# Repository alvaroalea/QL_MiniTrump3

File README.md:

# SINCLAIR QL Mini Trump Card 3 Disk Interface

(C) 2024 Alvaro Alea Fernandez

License under: CERN Open Hardware Licence Version 2 - Strongly Reciprocal

https://ohwr.org/cern_ohl_s_v2.txt

This is a new PCB for the well know Trump Card Interface.

WARNING: This board include a joke (not in the preview picture, surprise!) in the back skillscreen, I'm not political, it's only a game of words, if you do not like, you can remove the back skillscreen when order the PCB or ask me for gerbers without the joke, no problem.

## Advantages

This PCB add a passthrough conector to allow aditional interfaces. (compatibility is limited, not al signal are routed and boards that use the P'N'P mechanism of the QL only work with a Minerva ROM because Sinclair's ROM only search for 1 board)

It's also a lot smaller than original one.

It's use standar AT cable (with a twist) and standar AT disc drives (drives configures as 2nd unit)

## Drawbacks

But it do not have memory, you need a Memory Expansion, be aware that you should use only a 512Kb (total 640Kb) expansion, if you want to have a total of 896Kb (like the original trump card) you should use my expansion board, and connect after the trump card, also JP1 in this board and the equivalent jumper shall be soldered to allow the paging mechanism of the Trump Card.

It only support 2 Disk Drive, no way to use 3 or 4 Drives

For the GAL use the one in the GAL directory, compatible with GAL16V8 and ATF16V8, it's compiled with GALasm that you can found here: https://github.com/daveho/GALasm

# Technical Info

It work with WD1770 and WD1772 floppy disc controlllers.

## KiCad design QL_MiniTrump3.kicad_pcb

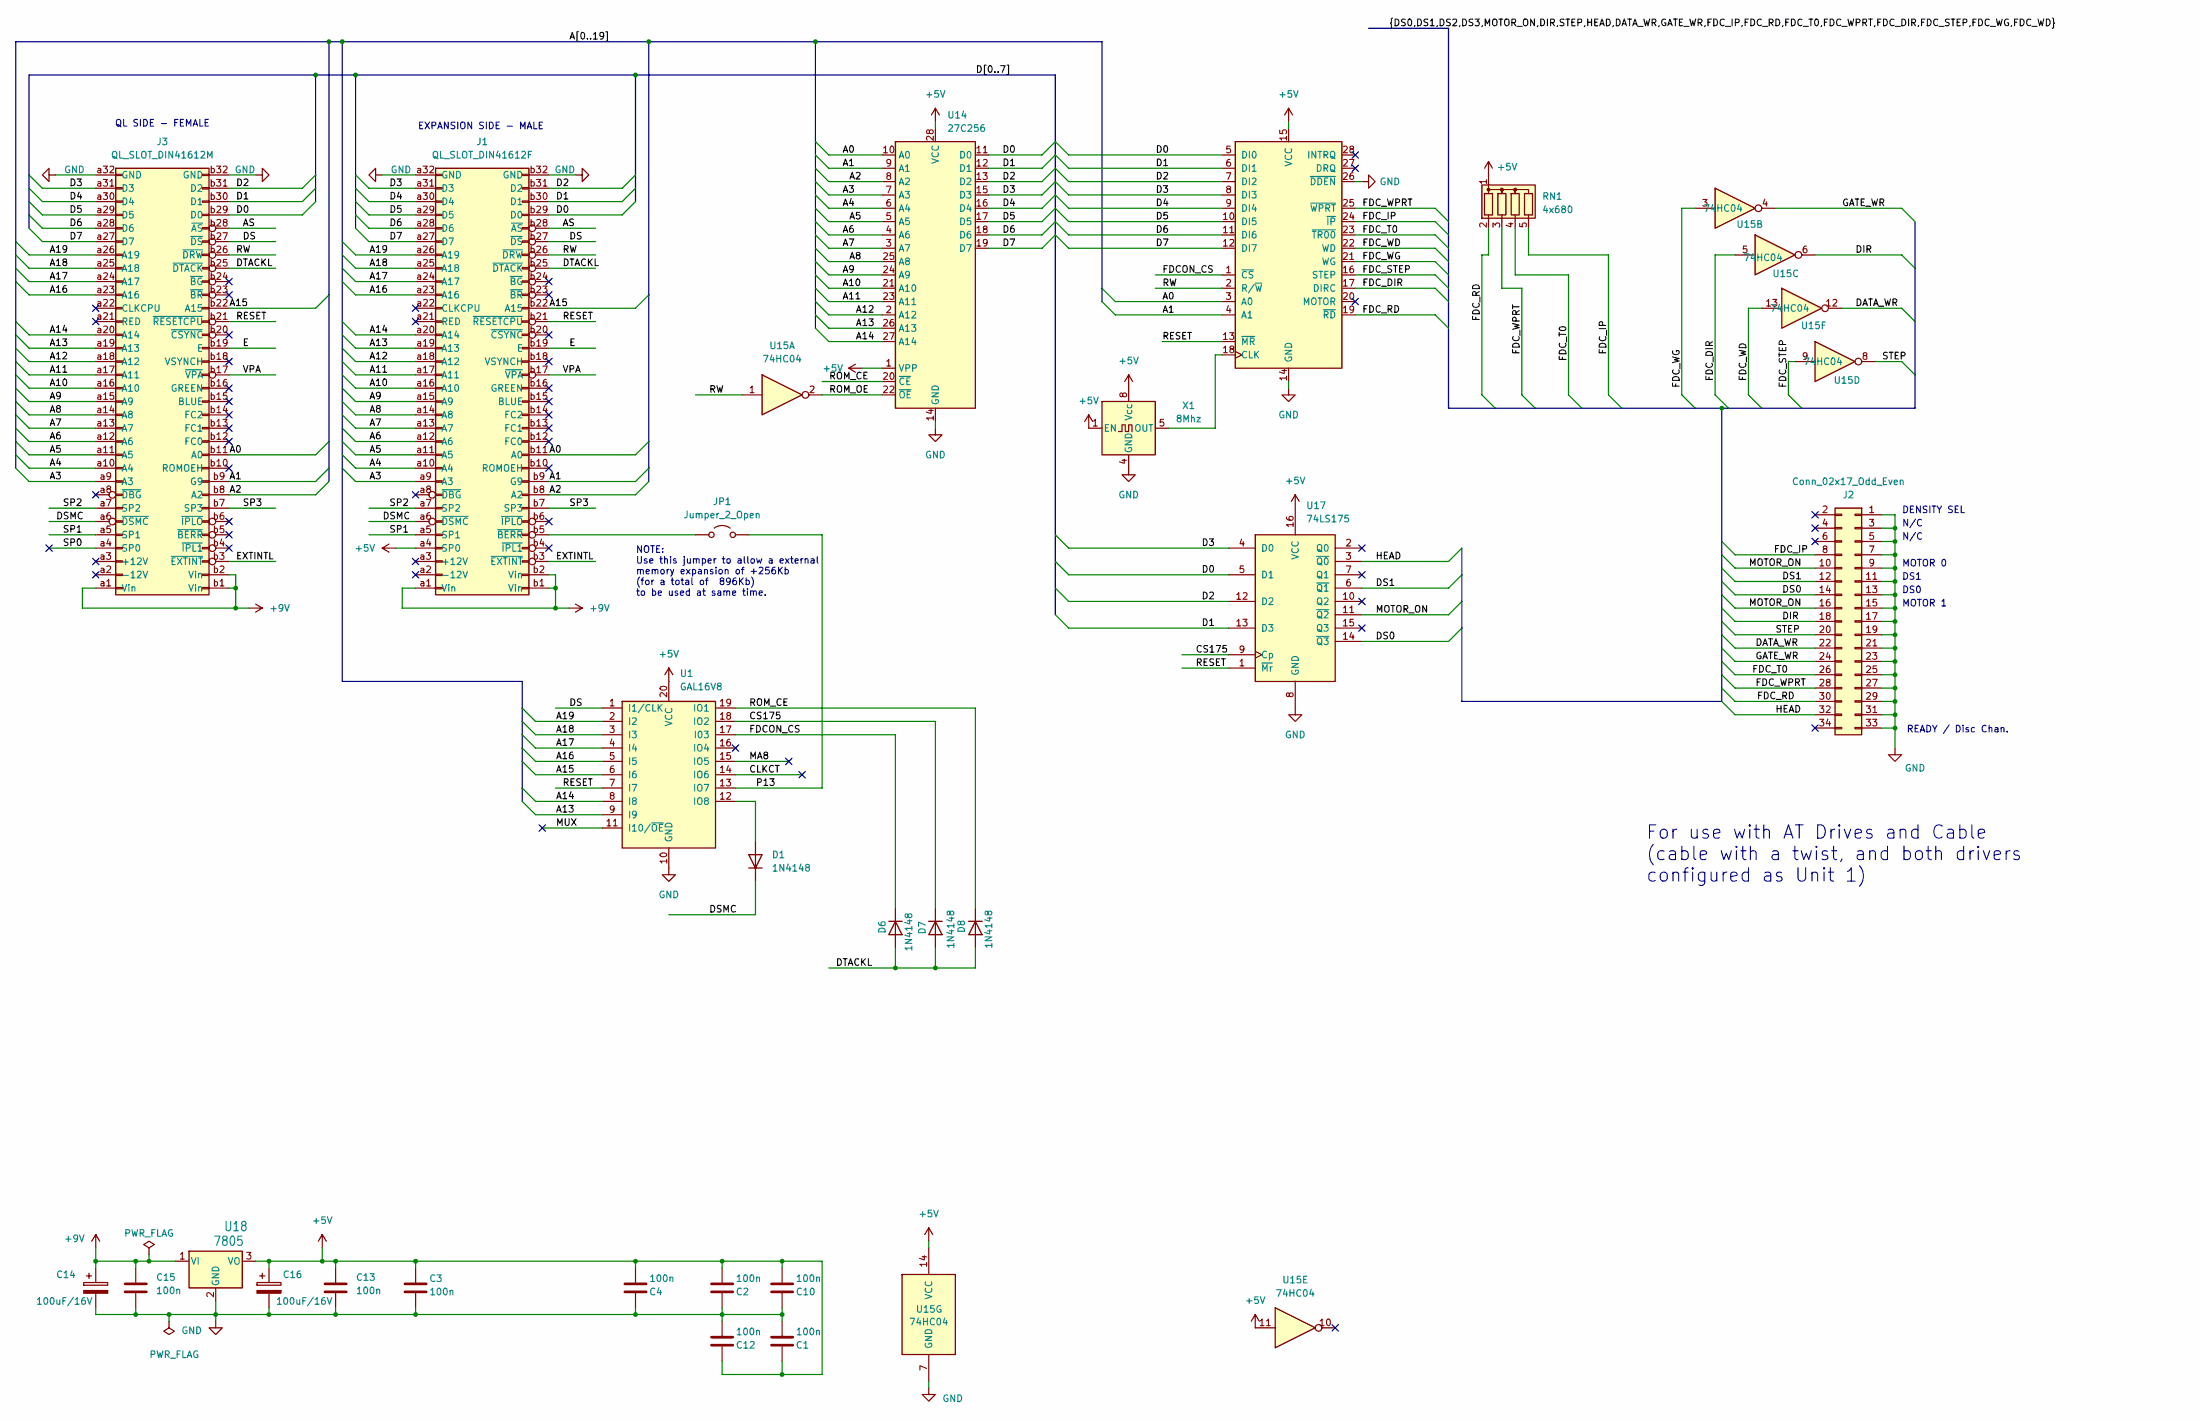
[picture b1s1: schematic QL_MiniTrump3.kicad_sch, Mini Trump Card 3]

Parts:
C1, C2, C3, C4, C10, C12, C13, C15: 100n; C_0805_2012Metric
C14, C16: 100uF/16V; CP_Elec_6.3x5.4
D1, D6, D7, D8: 1N4148; D_0805_2012Metric
J1: QL_SLOT_DIN41612F; DIN41612_B_2x32_Female_Horizontal_THT
J2: Conn_02x17_Odd_Even; PinHeader_2x17_P2.54mm_Vertical
J3: QL_SLOT_DIN41612M; DIN41612_B_2x32_Male_Horizontal_THT
JP1: Jumper_2_Open; SolderJumper-2_P1.3mm_Open_RoundedPad1.0x1.5mm
RN1: 4x680; R_Array_SIP5
U1: GAL16V8; DIP-20_W7.62mm
U13: FDC_WD1772; DIP-28_W15.24mm
U14: 27C256; DIP-28_W15.24mm
U15: 74HC04; DIP-14_W7.62mm
U17: 74LS175; DIP-16_W7.62mm
U18: 7805; TO-220-3_Horizontal_TabDown
X1: 8Mhz; Oscillator_DIP-8

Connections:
+5V: C1.1, C2.2, C3.2, C4.2, C10.2, C12.1, C13.1, C16.1, J1.a4 (SP0), RN1.1 (common), U1.20 (VCC), U13.15 (VCC), U14.1 (VPP), U14.28 (VCC), U15.11, U15.14 (VCC), U17.16 (VCC), U18.3 (VO), X1.1 (EN), X1.8 (Vcc)
+9V: C14.1, C15.1, J1.a1 (Vin), J1.b1 (Vin), J1.b2 (Vin), J3.a1 (Vin), J3.b1 (Vin), J3.b2 (Vin), U18.1 (VI)
/A0: J1.b11 (A0), J3.b11 (A0), U13.3 (A0), U14.10 (A0)
/A1: J1.b9 (G9), J3.b9 (G9), U13.4 (A1), U14.9 (A1)
/A2: J1.b8 (A2), J3.b8 (A2), U14.8 (A2)
/A3: J1.a9 (A3), J3.a9 (A3), U14.7 (A3)
/A4: J1.a10 (A4), J3.a10 (A4), U14.6 (A4)
/A5: J1.a11 (A5), J3.a11 (A5), U14.5 (A5)
/A6: J1.a12 (A6), J3.a12 (A6), U14.4 (A6)
/A7: J1.a13 (A7), J3.a13 (A7), U14.3 (A7)
/A8: J1.a14 (A8), J3.a14 (A8), U14.25 (A8)
/A9: J1.a15 (A9), J3.a15 (A9), U14.24 (A9)
/A10: J1.a16 (A10), J3.a16 (A10), U14.21 (A10)
/A11: J1.a17 (A11), J3.a17 (A11), U14.23 (A11)
/A12: J1.a18 (A12), J3.a18 (A12), U14.2 (A12)
/A13: J1.a19 (A13), J3.a19 (A13), U1.9 (I9), U14.26 (A13)
/A14: J1.a20 (A14), J3.a20 (A14), U1.8 (I8), U14.27 (A14)
/A15: J1.b22 (A15), J3.b22 (A15), U1.6 (I6)
/A16: J1.a23 (A16), J3.a23 (A16), U1.5 (I5)
/A17: J1.a24 (A17), J3.a24 (A17), U1.4 (I4)
/A18: J1.a25 (A18), J3.a25 (A18), U1.3 (I3)
/A19: J1.a26 (A19), J3.a26 (A19), U1.2 (I2)
/AS: J1.b28 (~AS), J3.b28 (~AS)
/CLKCT: U1.14 (IO6)
/CS175: D7.1 (K), U1.18 (IO2), U17.9 (Cp)
/D0: J1.b29 (D0), J3.b29 (D0), U13.5 (DI0), U14.11 (D0), U17.5 (D1)
/D1: J1.b30 (D1), J3.b30 (D1), U13.6 (DI1), U14.12 (D1), U17.13 (D3)
/D2: J1.b31 (D2), J3.b31 (D2), U13.7 (DI2), U14.13 (D2), U17.12 (D2)
/D3: J1.a31 (D3), J3.a31 (D3), U13.8 (DI3), U14.15 (D3), U17.4 (D0)
/D4: J1.a30 (D4), J3.a30 (D4), U13.9 (DI4), U14.16 (D4)
/D5: J1.a29 (D5), J3.a29 (D5), U13.10 (DI5), U14.17 (D5)
/D6: J1.a28 (D6), J3.a28 (D6), U13.11 (DI6), U14.18 (D6)
/D7: J1.a27 (D7), J3.a27 (D7), U13.12 (DI7), U14.19 (D7)
/DATA_WR: J2.22, U15.12
/DIR: J2.18, U15.6
/DS: J1.b27 (~DS), J3.b27 (~DS), U1.1 (I1/CLK)
/DS0: J2.14, U17.14 (~Q3)
/DS1: J2.12, U17.6 (~Q1)
/DSMC: D1.1 (K), J1.a6 (~DSMC), J3.a6 (~DSMC)
/DTACKL: D6.2 (A), D7.2 (A), D8.2 (A), J1.b25 (~DTACK), J3.b25 (~DTACK)
/E: J1.b19 (E), J3.b19 (E)
/EXTINTL: J1.b3 (~EXTINT), J3.b3 (~EXTINT)
/FDCON_CS: D6.1 (K), U1.17 (I03), U13.1 (~CS)
/FDC_DIR: U13.17 (DIRC), U15.5
/FDC_IP: J2.8, RN1.5 (R4), U13.24 (~IP)
/FDC_RD: J2.30, RN1.2 (R1), U13.19 (~RD)
/FDC_STEP: U13.16 (STEP), U15.9
/FDC_T0: J2.26, RN1.4 (R3), U13.23 (~TR00)
/FDC_WD: U13.22 (WD), U15.13
/FDC_WG: U13.21 (WG), U15.3
/FDC_WPRT: J2.28, RN1.3 (R2), U13.25 (~WPRT)
/GATE_WR: J2.24, U15.4
/HEAD: J2.32, U17.3 (~Q0)
/MA8: U1.15 (IO5)
/MOTOR_ON: J2.10, J2.16, U17.11 (~Q2)
/MUX: U1.11 (I10/~OE)
/P13: JP1.2 (B), U1.13 (IO7)
/RESET: J1.b21 (~RESETCPU), J3.b21 (~RESETCPU), U1.7 (I7), U13.13 (~MR), U17.1 (~Mr)
/ROM_CE: D8.1 (K), U1.19 (IO1), U14.20 (~CE)
/ROM_OE: U14.22 (~OE), U15.2
/RW: J1.b26 (~DRW), J3.b26 (~DRW), U13.2 (R/~W), U15.1
/SP0: J3.a4 (SP0)
/SP1: J1.a5 (SP1), J3.a5 (SP1)
/SP2: J1.a7 (SP2), J3.a7 (SP2)
/SP3: J1.b7 (SP3), J3.b7 (SP3)
/STEP: J2.20, U15.8
/VPA: J1.b17 (~VPA), J3.b17 (~VPA)
GND: C1.2, C2.1, C3.1, C4.1, C10.1, C12.2, C13.2, C14.2, C15.2, C16.2, J1.a32 (GND), J1.b32 (GND), J2.1, J2.3, J2.5, J2.7, J2.9, J2.11, J2.13, J2.15, J2.17, J2.19, J2.21, J2.23, J2.25, J2.27, J2.29, J2.31, J2.33, J3.a32 (GND), J3.b32 (GND), U1.10 (GND), U13.14 (GND), U13.26 (~DDEN), U14.14 (GND), U15.7 (GND), U17.8 (GND), U18.2 (GND), X1.4 (GND)
unnamed: D1.2 (A), U1.12 (IO8)
unnamed: J1.b5 (~BERR), JP1.1 (A)
unnamed: U13.18 (CLK), X1.5 (OUT)

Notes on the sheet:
QL SIDE - FEMALE
NOTE: Use this jumper to allow a external memory expansion of +256Kb (for a total of 896Kb) to be used at same time.
MOTOR 0
DS0
DS1
READY / Disc Chan.
MOTOR 1
N/C
For use with AT Drives and Cable (cable with a twist, and both drivers configured as Unit 1)
DENSITY SEL
EXPANSION SIDE - MALE

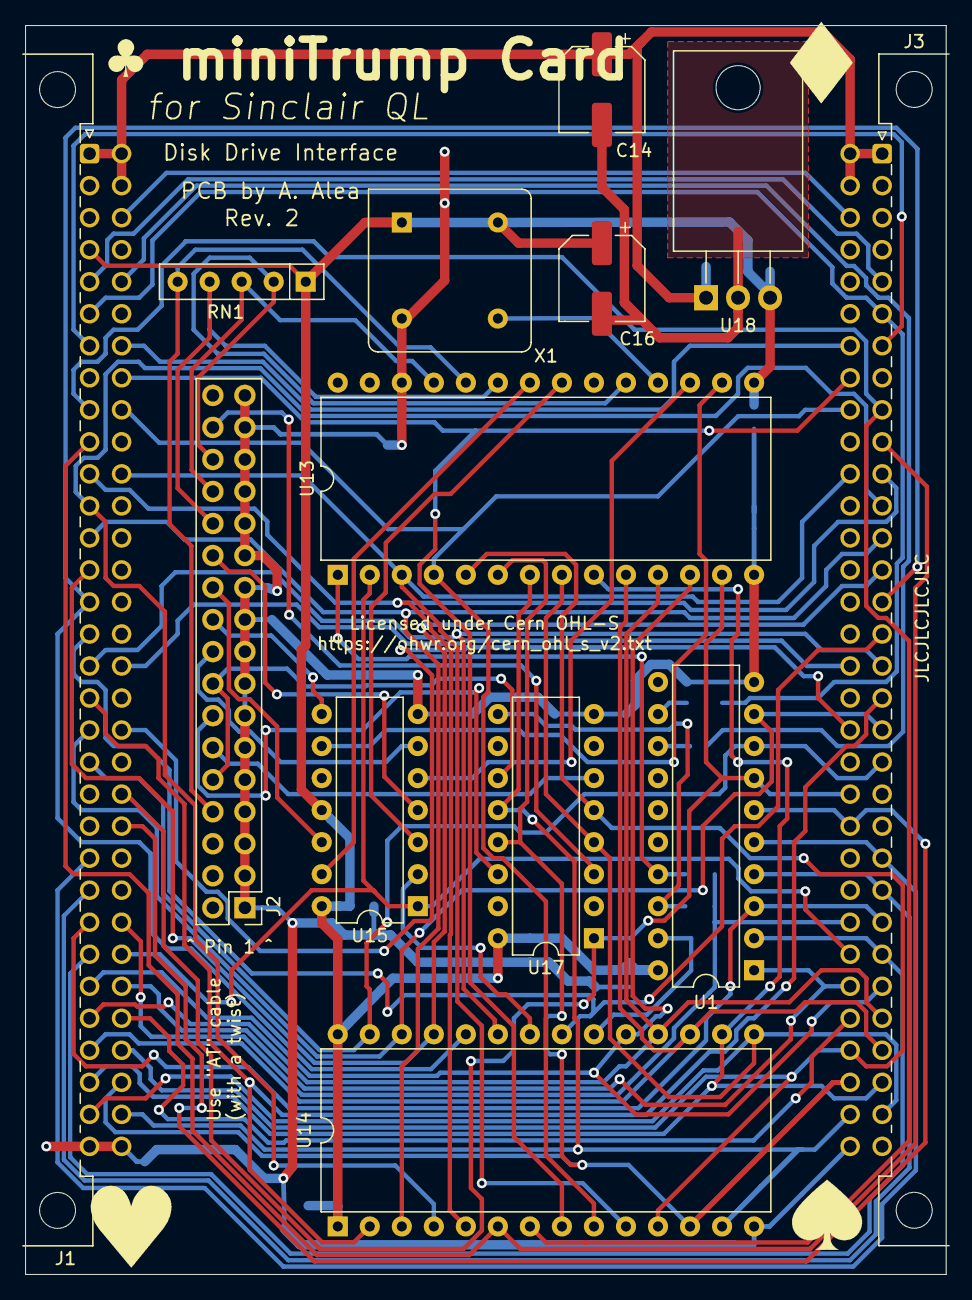
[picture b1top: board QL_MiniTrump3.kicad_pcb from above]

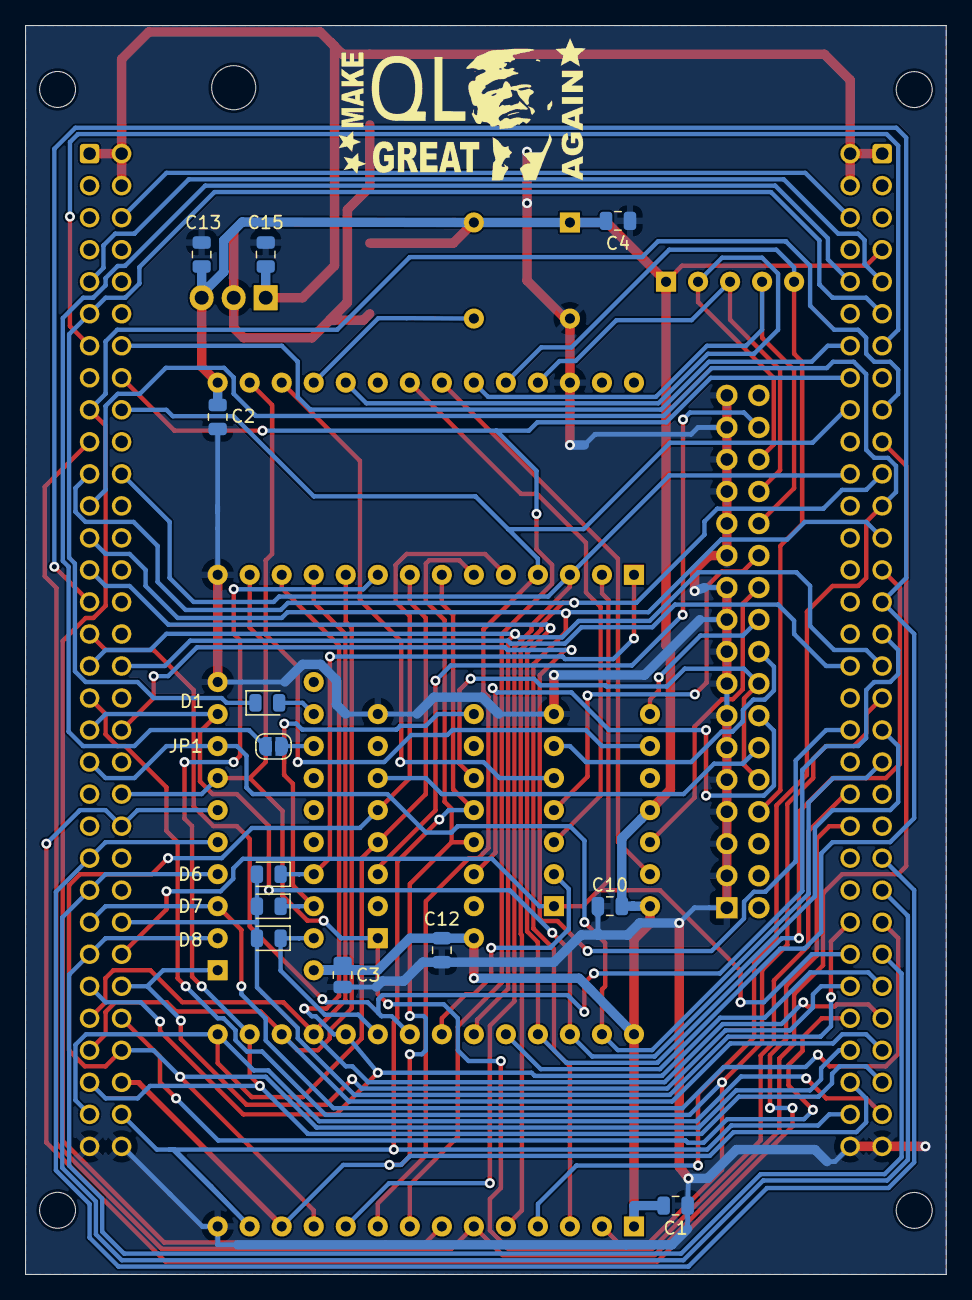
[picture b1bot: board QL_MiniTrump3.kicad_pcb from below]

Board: 2 copper layers, 73.0 x 99.1 mm, 26 parts (13 on the bottom side), 67 nets.

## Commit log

2024-05-07 real initial
2024-05-08 solucionada chapuza
2024-11-07 Rev 2, with GAL code
2024-11-15 update pic
2025-02-11 fix eprom reference, shall be 27C256

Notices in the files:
QL_MiniTrump3.kicad_pcb:
Licensed under Cern OHL-S
